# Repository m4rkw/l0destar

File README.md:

# l0destar

[l0destar.com](https://l0destar.com) A fully open-source vehicle tracker - open hardware and open software.

Inspired by the [Geolink Opentracker](https://github.com/geolink/opentracker/) and the [Fortebit Polaris](https://www.fortebit.tech/polaris/), the goal is to build something that will last: a reference design for the best possible vehicle tracker that anyone can fab, modify, and host. Hardware and software are completely open and maintained as a community project.

## Status

Prototyping / design phase. The v2.1 layout worked on a bench, and v2.6 (CAN,
K-line and micro), v3.0, v3.1, v3.2 and v3.3 have since been built and bench
tested - see the test status table in each board's README. v3.4 is designed
but not yet built or tested.

<strong>All boards before v3.3 have a serious defect in the K-wire circuit
if the L wire is connected. If any of these prototypes are built the L wire
should not be connected to the vehicle as if it was ever externally shorted
to the 12V rail the l0destar device would be damaged.</strong> Luckily very
few people are going to care at all about this ancient protocol and even fewer
will ever need the L wire in normal use but it still bears mentioning as an
indication that these are very much prototypes and there may be other
undiscovered defects.

## Disclaimer

This is a prototype, not a product. Nothing here is validated, qualified or certified, the parts lists are examples rather than a verified BOM, and any test results are my own unverified bench observations. All responsibility for anything built from it rests with the person building and installing it.

**Before building, installing or relying on any of this, read the [full disclaimer](DISCLAIMER.md).**

## What it is

- **Mission** - the world's best fully open-source vehicle tracker, no profit motive. See [`MISSION.md`](MISSION.md).
- **Goals** - KiCad reference design, open enclosure CAD, open firmware and server, weeks of standby on a typical car battery, 1 Hz GNSS, LTE-M/NB-IoT, CAN + K-Line diagnostics, accelerometer-driven wake. Full list in [`GOALS.md`](GOALS.md).
- **Technology choices** - Nordic nRF9151 SiP (LTE-M/NB-IoT + GNSS), LT8609A buck, ASM330LHHX IMU, MCP2518FD + TCAN3414 CAN, TJA1027T K-Line. Rationale and trade-offs in [`TECHNOLOGY.md`](TECHNOLOGY.md).

## License

l0destar is multi-licensed by artifact type - permissive across the board:

| Artifact | License |
|---|---|
| Hardware design files | `CERN-OHL-P-2.0` |
| Firmware | `Apache-2.0` |
| Server-side software | `Apache-2.0` |
| Documentation, enclosure CAD, media | `CC-BY-4.0` |

Full text and rationale in [`LICENSE.md`](LICENSE.md); license bodies in [`LICENSES/`](LICENSES/).

## Contributing

Contributions are welcome. l0destar uses the [Developer Certificate of Origin](https://developercertificate.org/) rather than a CLA - every commit must carry a `Signed-off-by:` trailer (`git commit -s`). See [`CONTRIBUTING.md`](CONTRIBUTING.md) for PR expectations.

## Contact

- Bug reports and feature ideas: [GitHub Issues](https://github.com/m4rkw/l0destar/issues)
- Open-ended questions and design discussion: [GitHub Discussions](https://github.com/m4rkw/l0destar/discussions)
- Direct contact: [contact me](https://l0destar.com/contact.html)

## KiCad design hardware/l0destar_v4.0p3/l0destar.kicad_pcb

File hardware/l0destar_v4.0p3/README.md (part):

# l0destar v4.0p3

## Overview

**NOTE: THIS HAS NOT BEEN TESTED, USE AT YOUR OWN RISK**

- This is a prototype l0destar vehicle tracker PCB designed to be
  hand-solderable (hot air required)
- It makes use of the [Makerdiary nRF9151 Connect Kit](https://makerdiary.com/products/nrf9151-connectkit) to provide the LTE and GPS
functions
- Component vias are dogleg-routed deliberately in order to keep the PCB costs
as low as possible
- The RF trace width is calculated using a standard 4-layer stackup at JLCPCB,
  different fabrication processes may require adjustment

## Disclaimer

This is a prototype, not a product. Nothing here is validated or certified,
the parts lists are examples rather than a verified BOM, and any test results
recorded below are my own unverified bench observations - repeat the testing
yourself rather than taking them on trust.

**Before building or installing anything from this repository, read the
[full disclaimer](../../DISCLAIMER.md).**

## New features

- The flash chip now has its own SPI bus
- Rail fault sensing on the GNSS backup supply

## Test status

| Item | Test | Result | Notes |
|---------|------|--------|-------|
| Input stage | 12V input reverse polarity | NOT TESTED | |
| Input stage | 12V ignition input reverse polarity | NOT TESTED | |
| INA238 | Voltage reading function | NOT TESTED | |
| Ignition presence | Ignition sense 3.3v signal | NOT TESTED | |
| LT8609 | 4.2V output | NOT TESTED | |
| LT8609 | UVLO thresholds | NOT TESTED | |
| MCU OVP | 4.2V passes through at nominal voltage | NOT TESTED | S11Q1 on, S12TP2 ≈ the buck output at S6C5 |
| MCU OVP | Cuts off when the buck output (S6C5) is driven above ~5V | NOT TESTED | Trip ≈ 4.95V, release ≈ 4.80V (calculated, see below) |
| MCU OVP | Scope trigger on VBAT rail, should never peak above abs max (~5.5V) during overvoltage condition | NOT TESTED | |
| GPS auxiliary 3.3V rail | Switches on enable signal | NOT TESTED | |
| CAN auxiliary 3.3V rail | Switches on CAN-enable signal | NOT TESTED | |
| K-line auxiliary 3.3V rail | Switches on K-enable signal | NOT TESTED | |
| K-line auxiliary 12V rail | Switches on K-enable signal | NOT TESTED | |
| Accelerometer | Operates while awake | NOT TESTED | |
| Accelerometer | Wake on motion | NOT TESTED | |
| GPS antenna bias tee | Obtains GPS signal | NOT TESTED | |
| K-wire | K wire connectivity | NOT TESTED | |
| CAN | Connectivity | NOT TESTED | |
| CAN standby via XSTBY signal | Low standby current | NOT TESTED | |
| Board | Quiescent current, GNSS backup supply off | | |
| Board | Quiescent current, GNSS backup supply on | | Reduces the TTFF from 17s to around 3s |

Note: the GNSS backup supply can be configured to enable on the first drive of a
day and then disable after a specific time (eg midnight) in order to conserve
power.

## Features

 - 12V live and 12V ignition inputs with TVS and reverse polarity protection
 - Enhanced input protection sized for pulse 2a at the ISO 7637-2:2011 maximum
 - Onboard 2A fusing
 - Ignition presence sensing
 - INA238 voltage reading
 - High efficiency buck converter
 - Auxiliary 3.3V rail for the GPS antenna bias tee
 - ASM330LHHXTR 6-axis IMU gyro/accelerometer
 - USB-C can be connected and disconnected for programming without any power
   disruption
 - Optional CAN interface
 - Optional K-wire (ISO 14230-1 K-line) interface - the wire carries KWP2000 (ISO 14230-4), the older
   ISO 9141-2, and manufacturer-specific pre-OBD protocols such as VAG KW1281
 - Auxiliary rail sensing/fault detection
 - MCU over-voltage protection on the 4.2V rail with fault-injection test point
 - I2C bus filtering against LTE TX bursts
 - Dedicated U-blox GPS module supporting BeiDou, Galileo, GLONASS, GPS / QZSS
- MX25R6435FZNIL0 64Mbit (8MB) SPI flash for data buffering / config

## Changes from v4.0p2

- K\_SLEEP tied to a pullup as there's no need for this to be GPIO controlled
- GNSS\_TIMEPULSE removed as this isn't used
- The flash chip no longer shares an SPI bus with the CAN circuit
- Added rail fault sensing on the GNSS backup supply

## Power supply

The Connect Kit can be powered through VBUS which would be much simpler as it
can take 5V, but then you have to disconnect the power before connecting a USB
cable. Same for the Nordic dev board - they both explicitly say not to connect
powered USB and VBUS at the same time. Because the intention is to install this
in a vehicle for testing the pragmatic decision was taken to power it with a
4.2V buck feeding the battery connector. With this power connection we can
connect USB-C at any time to update the firmware without needing to disconnect
power.

## Notes

 - All caps on the 12V rails must be >= 50V in order to handle transients
 - MCP2518FD with PP3V3\_CAN off - abs max on all I/O is VDD + 0.3V. Firmware
   must drive CAN\_SCK/SDI/CS low or tri-state them before dropping
   CAN\_ENABLE, or the nRF backfeeds the dead rail through the clamp diodes.
   Additionally, CAN\_CS and CAN\_INT have their pull-ups (S9R1, S9R2) on the
   switched rail, so both float when the domain is off - enable the nRF
   internal pulldown on those pins
 - K-line side, now its own domain - K\_ENABLE gates PP3V3\_K and PP12V\_K
   together. K\_TX lands on the TJA1027T, which is supplied from PP12V\_K
   (VBAT, pin 7), so driving it high with the rail down backfeeds the
   transceiver through its ESD clamps. K\_TX and K\_RX also carry 10K pull-ups
   (S10R2, S10R1) to PP3V3\_K, which float when that rail is down. Firmware
   must park K\_TX/K\_RX (low or tri-state) before dropping K\_ENABLE
 - The TJA1027T SLP\_N pin is not GPIO controlled: it is tied to PP3V3\_K
   through a 100K pull-up (S10R6), so the transceiver is awake whenever the
   K-line domain is powered. K\_ENABLE is the only way to put it to sleep
 - The OVP stage latches off while the unprotected rail stays above the
   release threshold. If the buck is genuinely faulted it will stay off; to
   clear a transient trip the input power has to drop far enough for the buck
   output to fall below ~4.8V
 - What the trip point has to protect: the 4.2V rail lands on the Connect Kit's
   battery connector (J2, MX1.25-2P), which goes to the **BAT pin of its
   BQ25180 charger** - not to the nRF9151 directly. On the BQ25180 only the IN
   pin is 25V tolerant; BAT and SYS are rated -0.3V to 5.5V absolute maximum.
   With no USB attached the BATFET conducts BAT to SYS, and SYS feeds nRF9151
   VDD through ferrite L4, so an over-voltage reaches the SiP as well - and the
   nRF9151 VDD absolute maximum is also 5.5V (VDD\_GPIO is a separate rail at
   3.9V). So 5.5V is the ceiling on both counts
 - S11R5/S11R6 set the trip point: V\_trip ≈ 2.5V × (1 + S11R5/S11R6) shifted
   slightly by S11R3. Nominal trip is ≈4.95V; worst case over the ATL431B's
   0.5% reference, 1% on S11R5/S11R6 and 5% on S11R3 the window is ≈4.87V to
   5.02V, so it stays clear of the buck's nominal 4.24V plus ripple at the
   bottom and keeps ~0.48V of margin to the 5.5V ceiling at the top. Keep the
   divider at 1% - a 5% pair widens that window at both ends
 - Indicated voltages and tolerances are the minimum, I generally always buy the
   tightest tolerances and highest voltages possible of everything as it's just
   simpler for managing inventory. Because of this, several of the "example"
   links will be to the parts I bought which might be tighter tolerance or
   higher voltage rating than the indicated minimum spec

## Bill of materials - required

| Item | Description | Specification | Example | Notes |
|------|-------------|---------------|---------|-------|
| MCU | MCU and GSM/GPS 40pin board | nRF9151 Connect Kit | [Makerdiary nRF9151 Connect Kit](https://makerdiary.com/products/nrf9151-connectkit) | |
| S1J1 | Molex Micro-fit 3.0 2x03 PCB connector | 43045-0600 | [43045-0600](https://uk.farnell.com/molex/43045-0600/conn-r-a-pcb-hdr-6pos-2row-3mm/dp/1012252) | |
| S1J2 | Makerdiary header 1 | 20-pin 2.54mm header | [20-pin pcb header](https://www.aliexpress.com/item/1005003610333849.html) | |
| S1J3 | Makerdiary header 2 | 20-pin 2.54mm header | [20-pin pcb header](https://www.aliexpress.com/item/1005003610333849.html) | |
| S1R1 | I2C pull-up resistor | 0402 1.8K 1% | [MCMR04X1801FTL](https://uk.farnell.com/multicomp-pro/mcmr04x1801ftl/res-1k8-1-0-0625w-0402-ceramic/dp/2072709) | |
| S1R2 | I2C pull-up resistor | 0402 1.8K 1% | [MCMR04X1801FTL](https://uk.farnell.com/multicomp-pro/mcmr04x1801ftl/res-1k8-1-0-0625w-0402-ceramic/dp/2072709) | |
| S1R3 | 100K pulldown resistor | 0402 100K 5% | [MCPWR02FTEP1003A](https://uk.farnell.com/multicomp-pro/mcpwr02ftep1003a/res-100k-1-thick-film-0402/dp/4538624) | |
| S1R4 | 100K pulldown resistor | 0402 100K 5% | [MCPWR02FTEP1003A](https://uk.farnell.com/multicomp-pro/mcpwr02ftep1003a/res-100k-1-thick-film-0402/dp/4538624) | |
| S1R5 | 100K pulldown resistor | 0402 100K 5% | [MCPWR02FTEP1003A](https://uk.farnell.com/multicomp-pro/mcpwr02ftep1003a/res-100k-1-thick-film-0402/dp/4538624) | |
| S1C1 | 100nF capacitor | 0402 >= 50V 10% X7R | [GRM155R71H104KE14D](https://uk.farnell.com/murata/grm155r71h104ke14d/cap-0-1-f-50v-10-x7r-0402/dp/2611912) | |
| S2F1 | 2A fuse | 1206 2A slow blow | [0407002.WRA](https://www.ebay.co.uk/itm/178539955750) | |
| S2F2 | 2A fuse | 1206 2A slow blow | [0407002.WRA](https://www.ebay.co.uk/itm/178539955750) | |
| S2Q1 | Reverse-polarity MOSFET | SQ2361 SOT-23 | [SQ2361CES-T1_BE3](https://www.ebay.co.uk/itm/178539853850) | |
| S2Q2 | Reverse-polarity MOSFET | SQJ457EP-T1_BE3 | [SQJ457EP-T1-GE3](https://www.ebay.co.uk/itm/178539865485) | |
| S2D1 | 15V Zener diode | BZX84C15 | [BZX84C15](https://uk.farnell.com/multicomp-pro/bzx84c15/zener-diode-0-3w-15v-sot-23/dp/2675186) | |
| S2D2 | 400W TVS diode | PTVS33VS1UTR,115 SOD-123W | [PTVS33VS1UTR,115](https://www.ebay.co.uk/itm/178539916580) | |
| S2D3 | 15V Zener diode | BZX84C15 | [BZX84C15](https://uk.farnell.com/multicomp-pro/bzx84c15/zener-diode-0-3w-15v-sot-23/dp/2675186) | |
| S2D4 | 400W TVS diode | PTVS33VS1UTR,115 SOD-123W | [PTVS33VS1UTR,115](https://www.ebay.co.uk/itm/178539916580) | |
| S2R1 | Pulldown resistor | 0402 1M 5% | [ERJ2RKF1004X](https://uk.farnell.com/panasonic/erj2rkf1004x/res-1m-1-0-1w-0402-thick-film/dp/2302957) | |
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
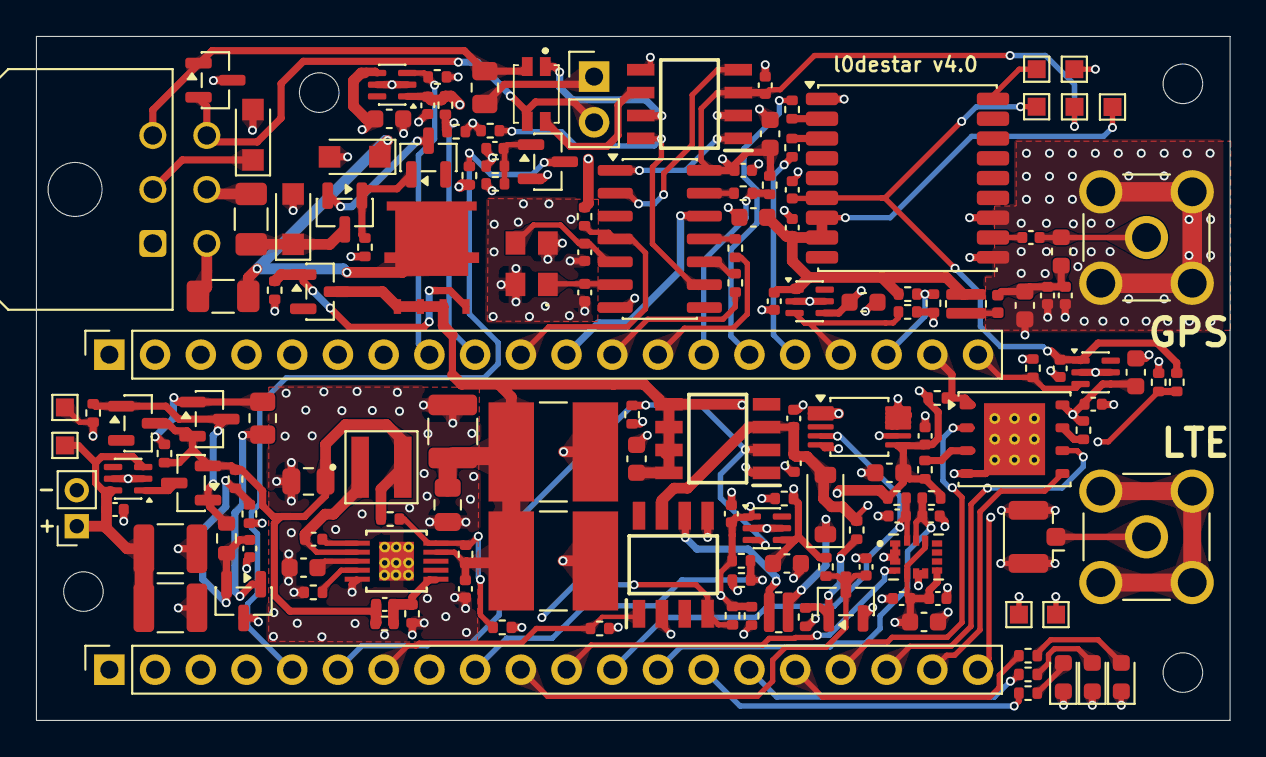
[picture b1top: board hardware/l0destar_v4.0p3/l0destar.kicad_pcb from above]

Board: 4 copper layers, 66.3 x 38.0 mm, 161 parts (0 on the bottom side), 89 nets.

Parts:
H1, H2, H3, H4: MountingHole; MountingHole_2.2mm_M2
S1C1, S3C2, S4C1, S6C1, S6C8, S7C2, S7C4, S7C9, S8C1, S8C3, S9C1, S9C4, S10C1, S16C2, S16C4, S16C5, S17C1: 0402 100nF 50V 10% X7R; C_0402_1005Metric
S1J1: Main connector; Molex_Micro-Fit_3.0_43045-0600_2x03_P3.00mm_Horizontal
S1J2: Conn_01x20_Socket; MakerDiary_nRF9151_ConnectKit_PinHeader_1-20_tight
S1J3: Conn_01x20_Socket_21-40; MakerDiary_nRF9151_ConnectKit_PinHeader_21-40_tight
S1J4: +; MakerDiary2PinHeader
S1R1, S1R2: 0402 1.8K 1%; R_0402_1005Metric
S1R3, S1R4, S1R5, S2R2, S7R3, S7R6, S7R7, S7R8, S7R10, S10R6, S16R1, S16R4: 0402 100K 5%; R_0402_1005Metric
S2C1, S2C2: 47uF 2220 50V 20% X7R; CAPC6050X550N
S2C3: 10uF 1210 50V 10% X7R SOFT TERMINATION; C_1210_3225Metric
S2D1, S2D3, S11D1: BZX84C15; SOT-23
S2D2, S2D4, S10D2: PTVS33VS1UTR,115; Nexperia_CFP3_SOD-123W
S2F1, S2F2: 0407002.WRA; Fuse_1206_3216Metric
S2Q1, S11Q1: SQ2361CES-T1_BE3; SOT-23
S2Q2: SQJ457EP-T1_BE3; POWERPAK-SO-8-4
S2R1, S7R4, S7R9, S7R11, S16R5: 0402 1M 5%; R_0402_1005Metric
S3C1, S6C2, S7C1, S7C3, S7C8, S15C4, S16C1, S16C3: 0603 2.2uF 25V 10% X7R; C_0603_1608Metric
S3U1: INA238; TSSOP-10_3x3mm_P0.5mm
S4Q1, S7Q1: 2N7002; SOT-23
S4R1, S7R5: 0402 180K 5%; R_0402_1005Metric
S4R2, S4R3: 0402 56K 5%; R_0402_1005Metric
S6C3: 0805 4.7uF 50V 10% X7R; C_0805_2012Metric
S6C4: 0402 10pF 50V C0G/NP0; C_0402_1005Metric
S6C5: 0805 22uF 10V 20% X7R; C_0805_2012Metric
S6L1: XFL4020-222ME; IND_XFL4020-222ME
S6R1: 0402 18.2K 1%; R_0402_1005Metric
S6R2: 0402 226K 1% ANTI-SULFUR AEC-Q200; R_0402_1005Metric
S6R3, S11R5: 0402 1M 1% ANTI-SULFUR AEC-Q200; R_0402_1005Metric
S6R4: 0402 0R JUMPER OR 1M 1% ANTI-SULFUR AEC-Q200; R_0402_1005Metric
S6R5: DNP 0402 243K 1% ANTI-SULFUR AEC-Q200; R_0402_1005Metric
S6R6: DNP 0402 3.92M 1%; R_0402_1005Metric
S6U1: LT8609AIMSE_PBF; LT8609AIMSE_WITH_GROUND_VIAS
S7C5, S7C7: 0402 1nF 50V 10% X7R; C_0402_1005Metric
S7C6: 0603 220nF 50V 10% X7R; C_0603_1608Metric
S7U1, S7U2, S7U4, S16U1: SiP32431DR3; SOT-363_SC-70-6
S7U3: ITS4060SSJNXUMA1
S8C2, S9C5: 0603 10uF 10V 20% X7R; C_0603_1608Metric
S8C4, S8C5, S15C2: 0402 100pF 50V 5% C0G/NP0; C_0402_1005Metric
S8R1: 0402 FB BLM15AG601SH1D; R_0402_1005Metric
S8U1: ASM330LHHXTR; XDCR_ASM330LHHXTR
S9C2, S9C3: 0402 27pF 10V 5% C0G/NP0; C_0402_1005Metric
S9D1: NUP2105L; SOT-23
S9FL1: ACT1210-101-2P-TL00; ACT12101012PTL00_tight
S9J1: Conn_01x02_Pin; PinHeader_1x02_P2.54mm_Vertical_Tight
S9R1, S9R2, S9R4, S10R1, S10R2, S17R1, S17R2, S17R3: 0402 10K 5%; R_0402_1005Metric
S9R3: 0805 120R 5% 0.5W; R_0805_2012Metric
S9R5, S13R1, S13R2, S13R3, S16R2, S16R3: 0402 1K 5%; R_0402_1005Metric
S9R6, S9R7: 0402 220R 5%; R_0402_1005Metric
S9U1: TCAN3414DR; SOIC127P600X175-8N
S9U2: MCP2518FD-xQBB; SOIC-14_3.9x8.7mm_P1.27mm
S9Y1: ECS-400-18-33-JGN-TR3; ECS4001833JGNTR3
S10D1: 1N4148W; D_SOD-123
S10R3: 0508 510R 5% 1W; R_0508_1220Metric_WideTerminal_Tight
S10U1: TJA1027T_20,118; TJA1027T_20_118
S11C1, S11C2: 1210 47uF 10V 20% X7R; C_1210_3225Metric
S11C3: 0402 3.3pF 50V C0G/NP0 +/- 0.25pF; C_0402_1005Metric
S11Q2: BC856BLT1G; SOT-23
S11R1: 0402 10K 1%; R_0402_1005Metric
S11R2: 0402 1M 1%; R_0402_1005Metric
S11R3: 0603 33M 5%; R_0603_1608Metric
S11R4: 0805 15K 1% ANTI-SULFUR AEC-Q200; R_0805_2012Metric
S11R6: 0402 1.05M 1%; R_0402_1005Metric
S11U1: LM66100DCK; SOT-363_SC-70-6
S11U2: ATL431BQDBZR; SOT-23
S12TP1: GND; TestPoint_Pad_1.0x1.0mm
S12TP2: 4.2V protected; TestPoint_Pad_1.0x1.0mm
S12TP3: 3.3V; TestPoint_Pad_1.0x1.0mm
S12TP4: 3.3V GNSS BCKP; TestPoint_Pad_1.0x1.0mm
S12TP5: 3.3V CAN; TestPoint_Pad_1.0x1.0mm
S12TP6: 3.3V K; TestPoint_Pad_1.0x1.0mm
S12TP7: 12V K; TestPoint_Pad_1.0x1.0mm
S13D1, S13D2, S13D3: Wurth 150060RS86000; LED_0603_1608Metric
S15C1: 0402 47pF 50V 5% C0G/NP0; C_0402_1005Metric
S15C3: 0402 10nF 50V 5% C0G/NP0; C_0402_1005Metric
S15FB1: 0402 600R 0.5A 25%; L_0402_1005Metric
S15J2: GPS_SMA; SAMTEC_SMA-J-P-H-RA-TH1_centrepin
S15J3: GSM_UFL; U.FL_Hirose_U.FL-R-SMT-1_Vertical
S15J4: GSM_SMA; SAMTEC_SMA-J-P-H-RA-TH1_centrepin
S15L1: LQW18AN68NJ00D; L_0603_1608Metric
S15R1: 0508 1W 5% 15R; R_0508_1220Metric_WideTerminal_Tight
S16TP1: 3.3V GNSS; TestPoint_Pad_1.0x1.0mm
S16TP2: SAFEBOOT_N; TestPoint_Pad_1.0x1.0mm
S16U2: MAX-M10S; ublox_MAX
S17U1: MX25R6435FZNIL0; WSON-8-1EP_6x5mm_P1.27mm_EP3.4x4mm_with_vias

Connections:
/FLASH_RESET: S17R3.2, S17U1.7 (~RESET/SIO3)
/FLASH_WP: S17R2.2, S17U1.3 (~WP/SIO2)
ACCELL_INT1: S1J2.11, S8U1.4 (INT1)
CAN_CS: S1J3.27 (Pin_14), S9R1.2, S9R5.1
CAN_ENABLE: S1J3.33 (Pin_8), S1R4.2, S7U2.3 (ON)
CAN_H: S1J1.3, S9D1.1 (K), S9FL1.2, S9R3.2
CAN_INT: S1J3.31 (Pin_10), S9R2.2, S9U2.4 (~INT)
CAN_L: S1J1.6, S9D1.2 (K), S9FL1.3, S9J1.2
CAN_SCK: S1J3.29 (Pin_12), S9R6.1
CAN_SDI: S1J3.28 (Pin_13), S9R7.1
CAN_SDO: S1J3.30 (Pin_11), S9U2.12 (SDO)
FLASH_CS: S1J3.22 (Pin_19), S17R1.2, S17U1.1 (~CS)
FLASH_SCK: S1J2.18, S17U1.6 (SCLK)
FLASH_SDI: S1J2.19, S17U1.5 (SI/SIO0)
FLASH_SDO: S1J2.17, S17U1.2 (SO/SIO1)
GND: S1C1.1, S1J1.1, S1J2.3 (GND), S1J3.39 (Pin_2), S1J4.2, S1R3.1, S1R4.1, S1R5.1, S2C1.2, S2C2.2, S2C3.2, S2D2.2 (A), S2D4.2 (A), S2R1.2, S2R2.2, S3C1.1, S3C2.1, S3U1.1 (A1), S3U1.2 (A0), S3U1.7 (GND), S4C1.2, S4Q1.2 (S), S4R2.1, S6C2.2, S6C3.2, S6C5.2, S6C8.2, S6R1.2, S6R2.2, S6R5.1, S6U1.5 (SYNC), S6U1.11 (GND), S7C1.2, S7C2.2, S7C3.2, S7C4.2, S7C5.2, S7C6.2, S7C7.2, S7C8.2, S7C9.2, S7Q1.2 (S), S7R4.1, S7R6.1, S7R9.1, S7R11.1, S7U1.2 (GND), S7U1.5 (GND), S7U2.2 (GND), S7U2.5 (GND), S7U3.1 (GND), S7U4.2 (GND), S7U4.5 (GND), S8C1.2, S8C2.2, S8C3.2, S8C4.2, S8C5.2, S8U1.1 (SDO/SA0), S8U1.2 (MSDA), S8U1.3 (MSCL), S8U1.6 (NC), S8U1.7 (GND), S9C1.2, S9C2.2, S9C3.2, S9C4.2, S9C5.2, S9D1.3 (A), S9R4.2, S9U1.2 (GND), S9U1.5 (SHDN), S9U2.7 (VSS), S9Y1.2 (GND_1), S9Y1.4 (GND_2), S10C1.1, S10D2.2 (A), S10U1.5 (GND), S11C1.2, S11C2.2, S11C3.1, S11R2.1, S11R6.1, S11U1.2 (GND), S11U1.5 (ST), S11U2.3 (ANODE), S12TP1.1 (1_1), S13D1.1 (K), S13D2.1 (K), S13D3.1 (K), S15C2.2, S15C3.2, S15C4.2, S15J2.2, S15J2.3, S15J2.4, S15J2.5, S15J3.2 (Ext), S15J4.2, S15J4.3, S15J4.4, S15J4.5, S16C1.2, S16C2.2, S16C3.2, S16C4.2, S16C5.2, S16R1.2, S16R5.2, S16U1.2 (GND), S16U1.5 (GND), S16U2.1 (GND), S16U2.10 (GND), S16U2.12 (GND), S17C1.2, S17U1.4 (GND), S17U1.9 (GND)
GNSS_BCKP_EN: S1J3.21 (Pin_20), S1R3.2, S7U1.3 (ON)
GNSS_ENABLE: S1J3.24 (Pin_17), S16R1.1, S16U1.3 (ON)
GNSS_RF: S15C1.1, S16U2.11 (RF_IN)
GNSS_RX: S1J3.26 (Pin_15), S16R2.1
GNSS_TX: S1J3.25 (Pin_16), S16R3.1
I2C_SCL: S1J2.13, S1R2.1, S3U1.5 (SCL), S8C5.1, S8U1.13 (SCL)
I2C_SDA: S1J2.12, S1R1.1, S3U1.4 (SDA), S8C4.1, S8U1.14 (SDA)
IGN_SENSE: S1J2.5 (P9), S4Q1.3 (D), S4R3.2
KWIRE_K: S1J1.2, S10D2.1 (K), S10R3.2, S10U1.6 (LIN)
K_ENABLE: S1J2.6, S1R5.2, S7U3.2 (IN), S7U4.3 (ON)
K_RX: S1J2.7, S10R1.2, S10U1.1 (RXD)
K_TX: S1J2.8, S10R2.2, S10U1.4 (TXD)
LED1: S1J2.14, S13R1.2
LED2: S1J2.15, S13R2.2
LED3: S1J2.16, S13R3.2
unnamed: S2D1.1 (A), S2Q1.1 (G), S2R1.1
unnamed: S2D2.1 (K), S2F1.1, S2Q1.3 (D)
unnamed: S2D3.1 (A), S2Q2.4, S2R2.1
unnamed: S2D4.1 (K), S2F2.2, S2Q2.5_0, S2Q2.5_1, S2Q2.5_2, S2Q2.5_3
unnamed: S4C1.1, S4Q1.1 (G), S4R1.2, S4R2.2
unnamed: S6C1.1, S6U1.1 (BST)
unnamed: S6R4.1, S6R5.2, S6R6.2, S6U1.10 (EN/UV)
unnamed: S6C4.1, S6R2.1, S6R3.1, S6U1.6 (FB)
unnamed: S6C2.1, S6U1.3 (INTVCC)
unnamed: S6R1.1, S6U1.4 (RT)
unnamed: S6C1.2, S6L1.1, S6U1.2 (SW)
unnamed: S7Q1.1 (G), S7R5.2, S7R6.2
unnamed: S8C1.1, S8C2.1, S8C3.1, S8R1.2, S8U1.5 (VDD_IO), S8U1.8 (VDD), S8U1.12 (CS)
unnamed: S9J1.1, S9R3.1
unnamed: S9FL1.1, S9U1.7 (CANH)
unnamed: S9FL1.4, S9U1.6 (CANL)
unnamed: S9U1.4 (RXD), S9U2.2 (RXCAN)
unnamed: S9R4.1, S9U1.8 (STBY), S9U2.9 (~INT0/GPIO0/XSTBY)
unnamed: S9U1.1 (TXD), S9U2.1 (TXCAN)
unnamed: S9C3.1, S9U2.6 (OSC1), S9Y1.1 (IN/OUT)
unnamed: S9C2.1, S9U2.5 (OSC2), S9Y1.3 (OUT/IN)
unnamed: S9R6.2, S9U2.10 (SCK)
unnamed: S9R7.2, S9U2.11 (SDI)
unnamed: S9R5.2, S9U2.13 (~CS)
unnamed: S10D1.1 (K), S10R3.1
unnamed: S10R6.1, S10U1.2 (SLP_N)
unnamed: S11D1.1 (A), S11Q1.1 (G), S11Q2.3, S11R2.2, S11R3.2
unnamed: S11Q2.1, S11R1.1, S11R4.2
unnamed: S11R4.1, S11U2.1 (CATHODE)
unnamed: S11C3.2, S11R3.1, S11R5.2, S11R6.2, S11U2.2 (REF)
unnamed: S13D1.2 (A), S13R1.1
unnamed: S13D2.2 (A), S13R2.1
unnamed: S13D3.2 (A), S13R3.1
unnamed: S15C2.1, S15C3.1, S15C4.1, S15FB1.2, S15L1.1
unnamed: S15FB1.1, S15R1.1
unnamed: S15J3.1 (In), S15J4.1
unnamed: S16R3.2, S16U2.3 (RXD)
unnamed: S16R2.2, S16U2.2 (TXD)
unnamed: S16TP2.1 (1_1), S16U2.18 (~SAFEBOOT)
PP3V3: S1J3.40 (Pin_1), S1R1.2, S1R2.2, S3C1.2, S3C2.2, S3U1.6 (VS), S4R3.1, S7C1.1, S7C3.1, S7C8.1, S7R7.2, S7U1.4 (IN), S7U2.4 (IN), S7U4.4 (IN), S8R1.1, S12TP3.1 (1_1), S16C1.1, S16U1.4 (IN), S17C1.1, S17R1.1, S17R2.1, S17R3.1, S17U1.8 (VCC)
PP3V3_CAN: S7C4.1, S7R3.1, S7U2.1 (OUT), S9C1.1, S9C4.1, S9C5.1, S9R1.1, S9R2.1, S9U1.3 (VDD), S9U2.14 (VDD), S12TP5.1 (1_1)
PP3V3_CAN_ST: S1J3.32 (Pin_9), S7R3.2, S7R4.2
PP3V3_GNSS: S15R1.2, S16C2.1, S16C3.1, S16C4.1, S16R4.1, S16TP1.1 (1_1), S16U1.1 (OUT), S16U2.7 (VCC_IO), S16U2.8 (VCC)
PP3V3_GNSS_BCKP: S7C2.1, S7R10.1, S7U1.1 (OUT), S12TP4.1 (1_1), S16C5.1, S16U2.6 (V_BCKP)
PP3V3_GNSS_BCKP_ST: S1J2.20, S7R10.2, S7R11.2
PP3V3_GNSS_ST: S1J3.23 (Pin_18), S16R4.2, S16R5.1
PP3V3_K: S7C9.1, S7R8.1, S7U4.1 (OUT), S10R1.1, S10R2.1, S10R6.2, S12TP6.1 (1_1)
PP3V3_K_ST: S1J2.9, S7R8.2, S7R9.2
PP4V2: S1C1.2, S1J4.1, S11C1.1, S11C2.1, S11U1.3 (~CE), S11U1.6 (VOUT), S12TP2.1 (1_1)
PP4V2_OVP_PROTECTED: S11Q1.3 (D), S11U1.1 (VIN)
PP4V2_UNPROTECTED: S6C4.2, S6C5.1, S6L1.2, S6R3.2, S6R6.1, S11D1.3 (K), S11Q1.2 (S), S11Q2.2, S11R1.2, S11R5.1
PP12V: S1J1.4, S2F2.1
PP12VI: S1J1.5, S2F1.2
PP12VIP: S2D1.3 (K), S2Q1.2 (S), S4R1.1
PP12VP: S2C1.1, S2C2.1, S2C3.1, S2D3.3 (K), S2Q2.1, S2Q2.2, S2Q2.3, S3U1.8 (Vbus), S3U1.9 (Vin-), S3U1.10 (Vin+), S6C3.1, S6C8.1, S6R4.2, S6U1.9 (VIN), S7C6.1, S7U3.5 (VS_1), S7U3.6 (VS_2), S7U3.7 (VS_3), S7U3.8 (VS_4)
PP12V_K: S7C5.1, S7R5.1, S7U3.3 (OUT), S10C1.2, S10D1.2 (A), S10U1.7 (VBAT), S12TP7.1 (1_1)
PP12V_K_ST: S1J2.10, S7C7.1, S7Q1.3 (D), S7R7.1
RF: S15C1.2, S15J2.1, S15L1.2

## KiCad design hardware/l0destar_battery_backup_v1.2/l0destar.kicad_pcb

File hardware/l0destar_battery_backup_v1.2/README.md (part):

# l0destar battery backup v1.2

## Overview

- This is a prototype inline battery backup module for the l0destar vehicle
  tracker. It sits in the harness between the car and the tracker and holds
  the tracker's supply at ~9V from a single CR123A lithium primary cell when
  car power is cut
- It is designed to be hand-solderable (hot air required). Every active part
  is in a leaded package: MSOP-12, SOT-23, TSOT-23, SC70, DPAK
- The cell is a **non-rechargeable** primary in a board-mounted holder.
  Nothing on the board charges it. See [Why a primary cell](#why-a-primary-cell)
- Pin-compatible with the v3.4 tracker's 2x3 Micro-Fit harness: J1 takes the
  car harness, J2 goes to the tracker, the CAN/K-line pins pass straight
  through and ignition passes through a diode (S1D1)
- 4-layer 63.1 x 36.2 mm board, JLC04161H-7628 stack-up, four M2 mounting
  holes. PCB DRC is clean and schematic ERC has only the cosmetic
  `endpoint_off_grid` warnings

## Changes from v1.1

1. External pin assignments updated for v4.0 boards

## Disclaimer

This is a prototype, not a product. Nothing here is validated or certified,
the parts lists are examples rather than a verified BOM, and every number
below is a desk calculation from datasheets rather than a bench measurement -
repeat the testing yourself rather than taking any of it on trust.

I strongly recommend not using unbranded CR123 cells or buying them from less
reputable sources.

**Before building or installing anything from this repository, read the
[full disclaimer](../../DISCLAIMER.md).**

## Test status

| Item | Test | Result | Notes |
|---------|------|--------|-------|
| Input stage | 12V car input reverse polarity | PASSED | S2Z1 conducts forward into S2F1, which should clear |
| Input stage | Pass-through drop VCAR to PPTRACKER, tracker asleep | PASSED | v1.0 dropped ~0.5V here. Expected ~20 mV, the LTC4412 regulated forward drop |
| Input stage | Pass-through drop VCAR to PPTRACKER at 50 mA and 250 mA | PASSED | Expected ~20 mV; S2Q1 is 15 mΩ so the regulation sets it, not R<sub>DS(on)</sub> |
| Switchover | Boost enables when the car rail falls below ~10.06V | PASSED | S6U1 with the 6.8M/909k divider |
| Switchover | Boost disables when the car rail returns above ~11V | PASSED | Depends on the cell voltage through S6R38/S6R39, see [Notes](#notes) |
| Boost | 9.6V output at S4C14/S4C15 | PASSED | 1.202V x (1 + 909k/130k) = 9.61V; ~9V at J2 after S2D2 |
| Cell | Reversed cell is harmless | PASSED | Not physically possible to install the cell backwards |
| Cell | No current ever flows into the cell | PASSED | Ammeter in series with the cell with the car present and during handover |
| Wake pulse | IGN pulse at boost start, car ignition wire connected and off | PASSED | Failed on v1.0. Expected ~12V peak, above 8V for ~0.4 s, at J2 pin 5, with S1D1 blocking the car pulldown |
| Wake pulse | Car ignition reaches the tracker | PASSED | J2 pin 5 should be one S1B drop below J1 pin 5 with the key on |
| Wake pulse | Sleeping tracker wakes and raises `backup power` | PASSED | Needs firmware with `CONFIG_APP_BACKUP_SUPPLY=y` |
| Board | Parked drain from the car with the cell fitted | PASSED | ~15 µA on top of the tracker's own draw |

## Features

 - Inline between the car harness and the tracker; CAN/K-line pass straight
   through, ignition through S1D1
 - ~15 µA quiescent draw from the car in pass-through: ~13 µA LTC4412HV plus
   the ~1.6 µA sense divider
 - Same input protection parts as the tracker: 2A time-lag fuse, 33V TVS
   sized to ride out suppressed load dump
 - Reverse polarity protection
 - Ideal diode pass-through (LTC4412HV + P-channel FET) with a ~20 mV drop
   down to sleep current
 - Synchronous boost (LTC3122) with true output disconnect: the backup rail
   is 0V while the car is present, so the cell is only ever loaded during a
   cut
 - Nanopower comparator switchover (TLV3012, 2.8 µA) running straight from
   the cell: takes over below ~10.06V on the car rail
 - No cell lockout: the boost runs the cell until it can't. It's a
   consumable primary, so there is nothing to protect
 - Ignition wake pulse: a cut wakes a sleeping tracker immediately instead of
   at its next timed wake, and the tracker reports the cut
 - Estimated runtime on a 1500 mAh CR123A: ~200 days idle, ~58 days
   reporting hourly, ~19 days reporting every 15 minutes
 - 3D-printable two-part enclosure with the cell accessible under the lid

## Why a primary cell

A non-rechargeable cell rather than a rechargeable pack, for three reasons:

- No rechargeable 18650-format cell is rated for storage in a sun-parked car.
  The binding limit is storage temperature (+45 °C at best for Li-ion and LFP;
  +20 °C beyond three months for LTO) and a parked car reaches ~70 °C cabin
  air. A CR123A is rated to +60/+70 °C
- Cycle life is not worth paying for. The backup cycles a handful of times a
  year
- A primary turns silent ageing into an event. The boost regulates its output,
  so the tracker cannot see cell voltage - a rechargeable's calendar fade would
  be invisible until a real theft tested it. The only thing that consumes a
  primary is a power cut the tracker already alerts on, so *"did it get
  used?"* is answered in the server's alert log

The cell is a consumable. A `backup power` alert that runs for a long time
means the cell needs replacing, since it does not recover. Taking the cell
out is the storage mode.

### Ignition wake pulse

A sleeping tracker has three wake sources: its timer, the accelerometer and
ignition-present. A power cut touches none of them, so on its own it would be
found at the next timed wake. The module therefore fakes ignition for a
moment when it takes over.

The tracker's wake is level-triggered and the firmware latches it, so the
pulse only has to trip the interrupt. On an ignition wake the firmware reads
the rail first: in the backup band it is the module's pulse, so the unit
reports at once with the `backup power` alert and goes back to sleep.

The car holds its ignition wire at ground when the key is off, which sank
the pulse on v1.0. S1D1 sits in series between the car's ignition (J1 pin 5)
and the tracker's (J2 pin 5) so the pulse only drives the tracker's input.
The cost is one silicon diode drop on the ignition signal the tracker sees.

Limits: a second cut within the ~40 s VBOOST decay gives no pulse and falls
back to the timed wake.

## Board configuration

### Connectors

Both connectors are the tracker's Molex Micro-Fit 3.0 2x3 (43045-0600) with
the v3.4 pinout. J1 is the car harness, J2 goes to the tracker.

| Pin | J1 (car) | J2 (tracker) | Notes |
|-----|----------|--------------|-------|
| 1 | SPARE | SPARE | Unused by v3.4, not connected on this board |
| 2 | GND | GND | |
| 3 | CAN\_H / K | CAN\_H / K | Passed straight through |
| 4 | +12V | +12V (PPTRACKER) | Car through the ideal diode, or ~9V from the boost on backup |
| 5 | IGN | IGN | Through S1D1 (one diode drop); the wake pulse is injected on the J2 side |
| 6 | CAN\_L / L | CAN\_L / L | Passed straight through |

### Firmware

The tracker needs `CONFIG_APP_BACKUP_SUPPLY=y`. With it, a supply between
`CONFIG_APP_BACKUP_MIN_MV` (8500) and `CONFIG_APP_BACKUP_MAX_MV` (9700) with
the ignition off is treated as backup power rather than a flat car battery:
timed reports keep going, the 11.8V power-off and 12.0V sleep-safety rules
are bypassed, a `backup power` alert is raised once and a `car power
restored` alert when the rail comes back. Without the module a car battery in
that band is flat, so leave it off on trackers that do not have one.

### Cell

The board carries a Keystone 1051 CR123A holder and nothing else as a cell
input. Fit a CR123A from one of the three big brands (Energizer 123 /
EL123AP, Panasonic CR123A, Duracell DL123A): all are high-rate Li-MnO2 cells,
1500-1550 mAh, rated for the ~130 mA typical / ~250 mA worst-case bursts the
boost draws. Mark polarity on the silk and the lid; a reversed cell is
harmless but gives no backup.

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
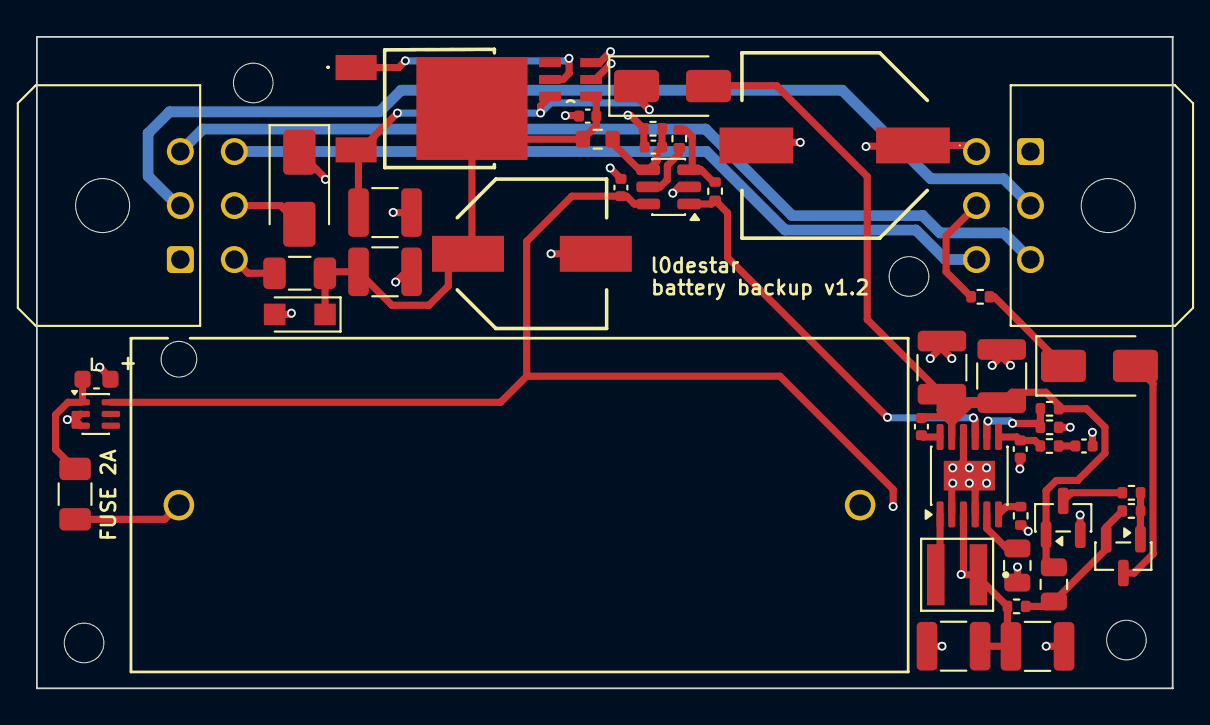
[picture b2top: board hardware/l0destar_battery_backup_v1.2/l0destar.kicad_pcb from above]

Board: 4 copper layers, 63.1 x 36.2 mm, 50 parts (0 on the bottom side), 30 nets.

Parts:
S1D1, S2D2, S5D3: S1B; D_SMA
S1H1, S1H2, S1H3, S1H4: MountingHole; MountingHole_2.2mm_M2
S1J1: Car harness; Molex_Micro-Fit_3.0_43045-0600_2x03_P3.00mm_Horizontal
S1J2: Tracker harness; Molex_Micro-Fit_3.0_43045-0600_2x03_P3.00mm_Horizontal
S2C1, S4C9, S6C2: 0402 100nF 50V 10% X7R; C_0402_1005Metric
S2C2: 47uF 63V - EEH-ZC1J470P; EEH_ZC1J470P
S2C4: 82uF 63V - HHXC630ARA820MJA0G; HHXC630ARA820MJA0G
S2C5, S2C6, S4C14, S4C15: 1210 10uF 50V X7R SOFT-TERM; C_1210_3225Metric
S2F1, S3F1: 0407002.WRA; Fuse_1206_3216Metric
S2Q1: SQD50P06-15L_GE3; SQD50P06-15L_GE3_tight
S2U1: LTC4412HVIS6PBF
S2Z1: PTVS33VS1UTR,115; Nexperia_CFP3_SOD-123W
S3BT1: CR123A; 1051_KEY
S3C1: 0603 2.2uF 25V 10% X7R; C_0603_1608Metric
S3U1: LM66100DCKR; SOT-363_SC-70-6
S4C7, S4C8: 1210 47uF 10V 20% X7R; C_1210_3225Metric
S4C11: 0402 560pF 50V 5% C0G/NP0; C_0402_1005Metric
S4C12: 0402 10pF 50V C0G/NP0; C_0402_1005Metric
S4C13, S5C17: 0805 4.7uF 50V 10% X7R; C_0805_2012Metric
S4L1: 2.2uH XFL4020-222MEC; IND_XFL4020-222ME
S4R14: 0402 57.6K 1%; R_0402_1005Metric
S4R18: 0402 200K 1%; R_0402_1005Metric
S4R19, S6R33: 0402 909K 1% ANTI-SULFUR AEC-Q200; R_0402_1005Metric
S4R20: 0402 130K 1%; R_0402_1005Metric
S4U5: LTC3122EMSE#PBF; MSOP-12-1EP_3x4.039mm_P0.65mm_EP1.651x2.845mm
S5Q6: 2N7002; SOT-23
S5Q7: BC856B; SOT-23
S5R21: 0402 10K 5%; R_0402_1005Metric
S5R22, S5R24, S5R25, S6R39: 0402 1M 1%; R_0402_1005Metric
S6C1: 0402 100pF 50V 5% C0G/NP0; C_0402_1005Metric
S6R32: 0603 6.8M 1%; R_0603_1608Metric
S6R38: 0402 47K 5%; R_0402_1005Metric
S6U1: TLV3012AIDBVR; SOT-23-6

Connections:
CAN_H: S1J1.3, S1J2.3
CAN_L: S1J1.6, S1J2.6
EN_BOOST: S4U5.9 (SD), S6R39.1, S6U1.1 (OUT)
GND: S1J1.1, S1J2.1, S2C1.2, S2C2.2 (-), S2C4.2 (-), S2C5.2, S2C6.2, S2U1.2 (GND), S2U1.3 (CTL), S2Z1.2 (A), S3BT1.2, S3C1.2, S3U1.2 (GND), S3U1.3 (~CE), S4C7.2, S4C8.2, S4C11.2, S4C12.2, S4C13.2, S4C14.2, S4C15.2, S4R14.2, S4R20.2, S4U5.2 (PGND), S4U5.4 (PWM/SYNC), S4U5.10 (SGND), S4U5.13 (EP), S5Q6.2 (S), S6C1.2, S6C2.2, S6R33.2, S6U1.2 (V-)
IGN: S1D1.1 (K), S1J2.5, S5R21.2
IGN_CAR: S1D1.2 (A), S1J1.5
KWIRE_K: S1J1.2, S1J2.2
unnamed: S2Q1.1 (G), S2U1.5 (GATE)
unnamed: S3BT1.1, S3F1.1
unnamed: S3C1.1, S3F1.2, S3U1.1 (VIN)
unnamed: S4C11.1, S4R18.2
unnamed: S4C9.1, S4U5.12 (CAP)
unnamed: S4R19.2, S4R20.1, S4U5.8 (FB)
unnamed: S4R14.1, S4U5.6 (RT)
unnamed: S4L1.2, S4U5.1 (SW)
unnamed: S4C12.1, S4R18.1, S4U5.7 (VC)
unnamed: S4C13.1, S4U5.5 (VCC)
unnamed: S5D3.2 (A), S5Q7.3 (C)
unnamed: S5D3.1 (K), S5R21.1
unnamed: S5Q6.3 (D), S5R24.2
unnamed: S5Q7.1 (B), S5R24.1, S5R25.2
unnamed: S5C17.1, S5Q7.2 (E), S5R22.2, S5R25.1
unnamed: S6R38.2, S6R39.2, S6U1.3 (IN+)
unnamed: S6C1.1, S6R32.2, S6R33.1, S6U1.4 (IN-)
unnamed: S6R38.1, S6U1.5 (REF)
PP12V: S1J1.4, S2F1.1
PPTRACKER: S1J2.4, S2C4.1 (+), S2C5.1, S2D2.1 (K), S2Q1.3 (S), S2U1.6 (SENSE)
VBAT: S3U1.6 (VOUT), S4C7.1, S4C8.1, S4L1.1, S4U5.3 (VIN), S5R22.1, S6C2.1, S6U1.6 (V+)
VBOOST: S2D2.2 (A), S4C9.2, S4C14.1, S4C15.1, S4R19.1, S4U5.11 (VOUT), S5C17.2, S5Q6.1 (G)
VCAR: S2C1.1, S2C2.1 (+), S2C6.1, S2F1.2, S2Q1.2 (D), S2U1.1 (VIN), S2Z1.1 (K), S6R32.1

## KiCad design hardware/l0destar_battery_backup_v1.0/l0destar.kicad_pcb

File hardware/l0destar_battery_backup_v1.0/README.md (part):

# l0destar battery backup v1.0

## Overview

**NOTE: THIS HAS NOT YET BEEN BUILT OR TESTED, USE AT YOUR OWN RISK**

- This is a prototype inline battery backup module for the l0destar vehicle
  tracker. It sits in the harness between the car and the tracker and holds
  the tracker's supply at ~9V from a single CR123A lithium primary cell when
  car power is cut
- It is designed to be hand-solderable (hot air required). Every active part
  is in a leaded package: MSOP-12, SOT-23, SC70, VSSOP-8, DPAK
- The cell is a **non-rechargeable** primary in a board-mounted holder.
  Nothing on the board charges it. See [Why a primary cell](#why-a-primary-cell)
- Pin-compatible with the v3.4 tracker's 2x3 Micro-Fit harness: J1 takes the
  car harness, J2 goes to the tracker, and the CAN/K-line and ignition pins pass
  straight through
- 4-layer 63.1 x 36.2 mm board, JLC04161H-7628 stack-up, four M2 mounting
  holes. Schematic ERC and PCB DRC are clean apart from the expected items
  listed under [Notes](#notes)

## Disclaimer

This is a prototype, not a product. Nothing here is validated or certified,
the parts lists are examples rather than a verified BOM, and every number
below is a desk calculation from datasheets rather than a bench measurement -
repeat the testing yourself rather than taking any of it on trust.

I strongly recommend not using unbranded CR123 cells or buying them from less
reputable sources.

**Before building or installing anything from this repository, read the
[full disclaimer](../../DISCLAIMER.md).**

## Test status

| Item | Test | Result | Notes |
|---------|------|--------|-------|
| Input stage | 12V car input reverse polarity | NOT TESTED | S1U1/S1Q1 ideal diode blocks; S1Z1 conducts forward into S1F1, which should clear |
| Input stage | Pass-through drop VCAR to PPTRACKER at 50 mA and 250 mA | NOT TESTED | Expected tens of mV through S1Q1 (27 mΩ), with brief body-diode drops while the LM74610 charge pump recharges |
| Input stage | ISO 7637-2 pulse 2a and 35V load dump ride-through | NOT TESTED | S1Z1 is the tracker's 33V TVS; S1C2 47 µF + S1C6 10 µF + S1C1 on VCAR |
| Switchover | Boost enables when the car rail falls below ~10.06V | NOT TESTED | S5U1 with the 6.8M/909k divider |
| Switchover | Boost disables when the car rail returns above ~11V | NOT TESTED | Depends on the cell voltage through S5R38/S5R39, see [Notes](#notes) |
| Switchover | PPTRACKER dip during handover under a forced LTE burst | NOT TESTED | Scope on J2 pin 4; S1C4 100 µF + S1C5 10 µF carry the gap |
| Boost | 9.6V output at S4C14/S4C15 | NOT TESTED | 1.202V x (1 + 909k/130k) = 9.61V; ~9V at J2 after S1D2 |
| Boost | Output current at a 2.5V cell | NOT TESTED | Burst Mode limits to ~190 mA at 2.5V in, ~300 mA at 3V in (datasheet curves) |
| Boost | Bode plot and load step | NOT TESTED | Compensation is the datasheet 2xAA to 12V example, not tuned for this operating point |
| Cell lockout | Boost held off below 2.45V, released above 2.52V | NOT TESTED | S5U4 with 1M/1M divider and 33M feedback; test on a bench supply in place of the cell |
| Cell lockout | Re-enable paced ~0.3 s | NOT TESTED | S5R41/S5C7; S5D1 makes the disable immediate |
| Cell | Reversed cell is harmless | NOT TESTED | S3U1 blocks, VBAT sits at 0V, no backup |
| Cell | No current ever flows into the cell | NOT TESTED | Ammeter in series with the cell with the car present and during handover |
| Wake pulse | IGN pulse at boost start | NOT TESTED | Expected ~12V peak, above 8V for ~0.4 s, at J2 pin 5 |
| Wake pulse | Sleeping tracker wakes and raises `backup power` | NOT TESTED | Needs firmware with `CONFIG_APP_BACKUP_SUPPLY=y` |
| Board | Idle draw from the cell, tracker asleep | NOT TESTED | Expected ~280 µA at a 2.9V cell |
| Board | Parked drain from the car with the cell fitted | NOT TESTED | Expected ~1.6 µA from the 7.7M sense divider on top of the tracker's own draw |
| Enclosure | Board and cell fit, lid clearance over the cell | NOT TESTED | 1.9 mm above the cell by the datasheet, see [enclosure/](enclosure/) |

## Features

 - Inline between the car harness and the tracker; CAN/K-line and ignition
   pass straight through
 - ~5-10uA quiescent current in pass-through operation (untested)
 - Same input protection parts as the tracker: 2A time-lag fuse, 33V TVS
   sized to ride out suppressed load dump
 - Reverse polarity protection
 - Synchronous boost (LTC3122) with true output disconnect: the backup rail
   is 0V while the car is present, so the cell is only ever loaded during a
   cut
 - Nanopower comparator switchover (2 x TLV3012, 2.8 µA each) running
   straight from the cell: takes over below ~10.06V on the car rail
 - Cell undervoltage lockout at 2.45V with a paced restart, so a tired cell
   is stopped a few percent above its rated end voltage rather than flattened
 - Ignition wake pulse: a cut wakes a sleeping tracker immediately instead of
   at its next timed wake, and the tracker reports the cut
 - Estimated runtime on a 1500 mAh CR123A: ~200 days idle, ~58 days
   reporting hourly, ~19 days reporting every 15 minutes
 - 3D-printable two-part enclosure with the cell accessible under the lid

## Why a primary cell

A non-rechargeable cell rather than a rechargeable pack, for three reasons:

- No rechargeable 18650-format cell is rated for storage in a sun-parked car.
  The binding limit is storage temperature (+45 °C at best for Li-ion and LFP;
  +20 °C beyond three months for LTO) and a parked car reaches ~70 °C cabin
  air. A CR123A is rated to +60/+70 °C
- Cycle life is not worth paying for. The backup cycles a handful of times a
  year
- A primary turns silent ageing into an event. The boost regulates its output,
  so the tracker cannot see cell voltage - a rechargeable's calendar fade would
  be invisible until a real theft tested it. The only thing that consumes a
  primary is a power cut the tracker already alerts on, so *"did it get
  used?"* is answered in the server's alert log

The cell is a consumable. A `backup power` alert that runs for a long time
means the cell needs replacing, since it does not recover. Taking the cell
out is the storage mode.

### Ignition wake pulse

A sleeping tracker has three wake sources: its timer, the accelerometer and
ignition-present. A power cut touches none of them, so on its own it would be
found at the next timed wake. The module therefore fakes ignition for a
moment when it takes over.

The tracker's wake is level-triggered and the firmware latches it, so the
pulse only has to trip the interrupt. On an ignition wake the firmware reads
the rail first: in the backup band it is the module's pulse, so the unit
reports at once with the `backup power` alert and goes back to sleep.

Limits: a second cut within the ~40 s VBOOST decay, or a cut with the key on
and the ignition wire loaded by the car, gives no pulse; both fall back to
the timed wake.

## Board configuration

### Connectors

Both connectors are the tracker's Molex Micro-Fit 3.0 2x3 (43045-0600) with
the v3.4 pinout. J1 is the car harness, J2 goes to the tracker.

| Pin | J1 (car) | J2 (tracker) | Notes |
|-----|----------|--------------|-------|
| 1 | SPARE | SPARE | Unused by v3.4, not connected on this board |
| 2 | GND | GND | |
| 3 | CAN\_H / K | CAN\_H / K | Passed straight through |
| 4 | +12V | +12V (PPTRACKER) | Car through the ideal diode, or ~9V from the boost on backup |
| 5 | IGN | IGN | Passed straight through; the wake pulse is injected here |
| 6 | CAN\_L / L | CAN\_L / L | Passed straight through |

### Firmware

The tracker needs `CONFIG_APP_BACKUP_SUPPLY=y`. With it, a supply between
`CONFIG_APP_BACKUP_MIN_MV` (8500) and `CONFIG_APP_BACKUP_MAX_MV` (9700) with
the ignition off is treated as backup power rather than a flat car battery:
timed reports keep going, the 11.8V power-off and 12.0V sleep-safety rules
are bypassed, a `backup power` alert is raised once and a `car power
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
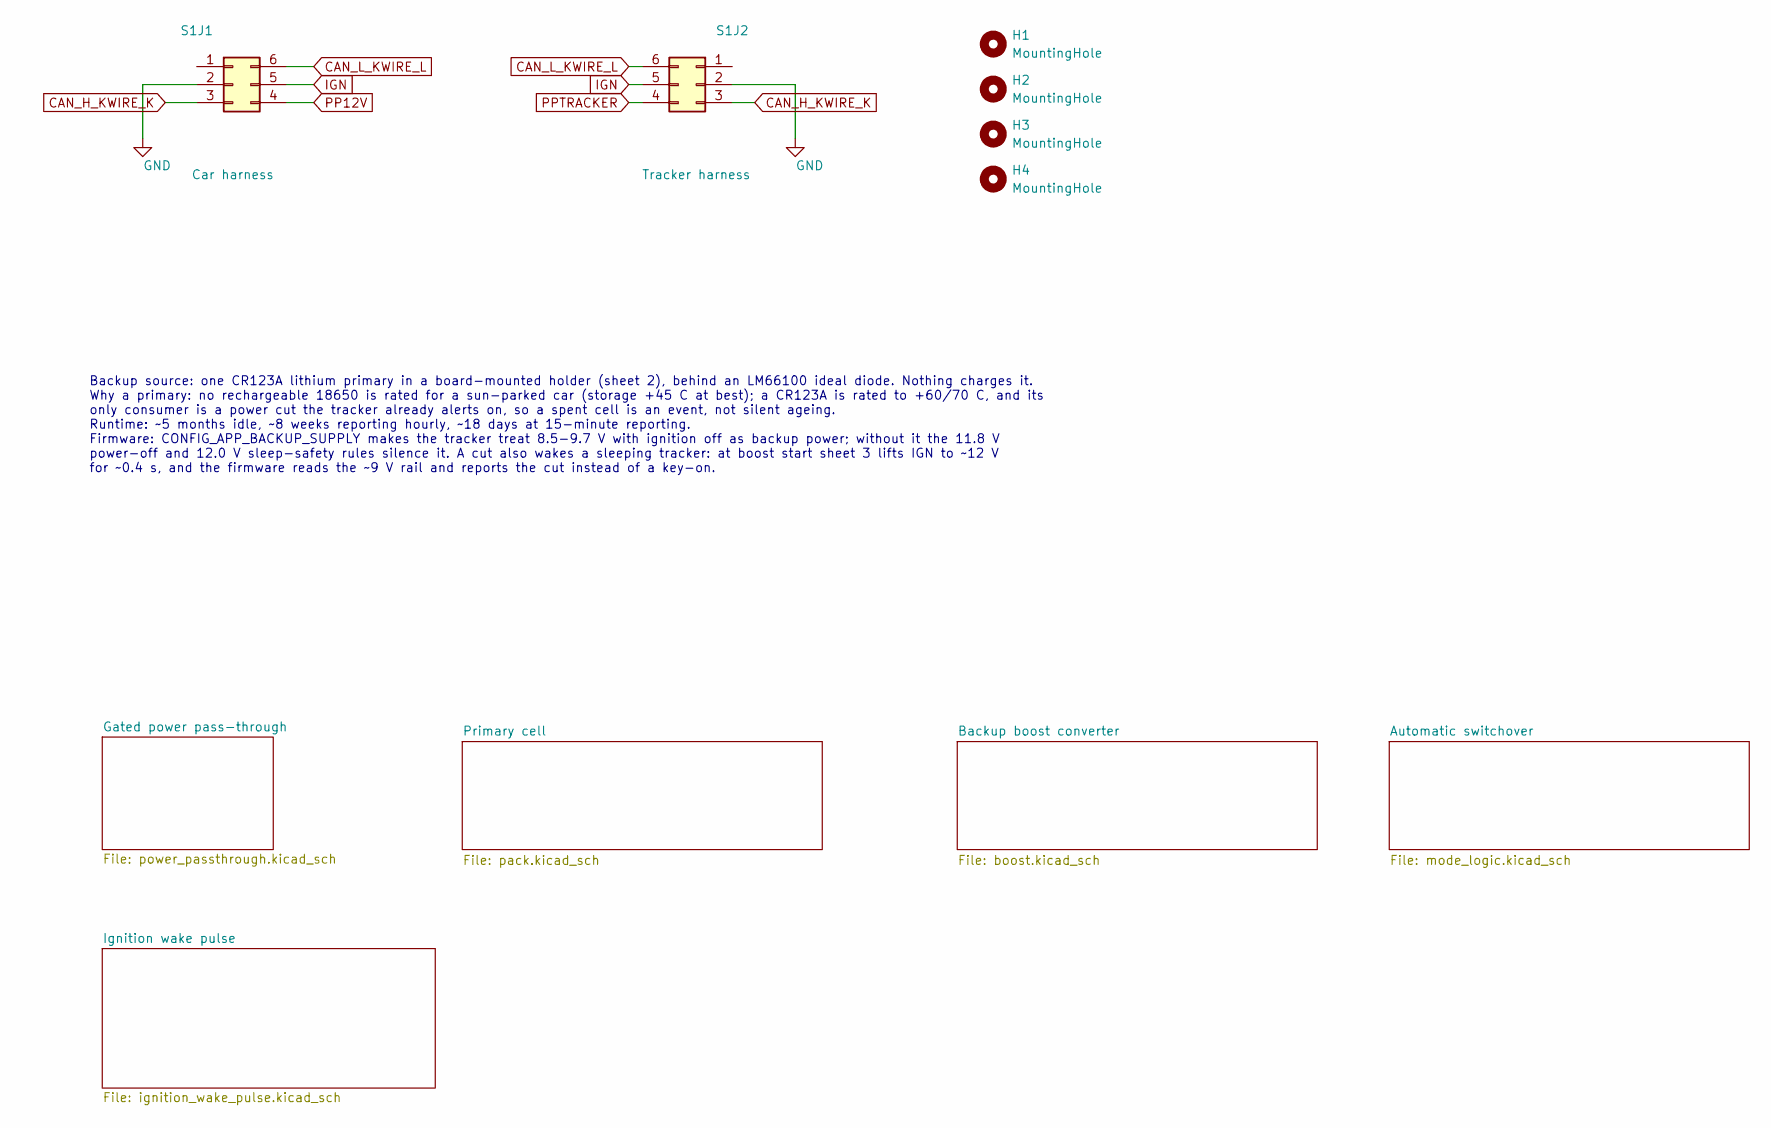
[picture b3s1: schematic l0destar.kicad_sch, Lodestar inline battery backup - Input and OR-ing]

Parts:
H1, H2, H3, H4: MountingHole; MountingHole_2.2mm_M2
S1J1: Car harness; Molex_Micro-Fit_3.0_43045-0600_2x03_P3.00mm_Horizontal
S1J2: Tracker harness; Molex_Micro-Fit_3.0_43045-0600_2x03_P3.00mm_Horizontal

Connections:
CAN_H_KWIRE_K: S1J1.3, S1J2.3
CAN_L_KWIRE_L: S1J1.6, S1J2.6
GND: S1J1.2, S1J2.2; also elsewhere on the board
IGN: S1J1.5, S1J2.5; also elsewhere on the board
PP12V: S1J1.4; also elsewhere on the board
PPTRACKER: S1J2.4; also elsewhere on the board

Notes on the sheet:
Backup source: one CR123A lithium primary in a board-mounted holder (sheet 2), behind an LM66100 ideal diode. Nothing charges it. Why a primary: no rechargeable 18650 is rated for a sun-parked car (storage +45 C at best); a CR123A is rated to +60/70 C, and its only consumer is a power cut the track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

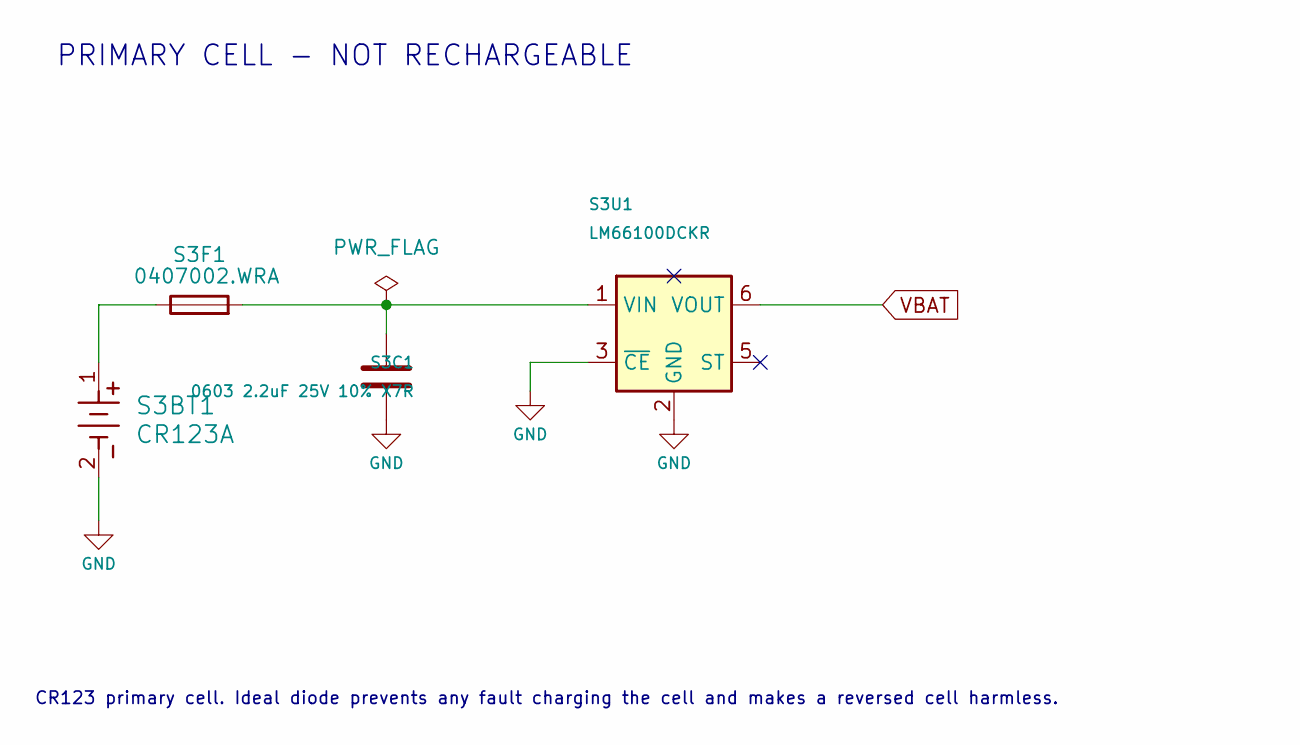
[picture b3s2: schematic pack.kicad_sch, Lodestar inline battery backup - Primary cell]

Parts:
S3BT1: CR123A; 1051_KEY; MPN 1051
S3C1: 0603 2.2uF 25V 10% X7R; C_0603_1608Metric; MPN GRM188Z71E225KE43D
S3F1: 0407002.WRA; Fuse_1206_3216Metric; MPN 0407002.WRA
S3U1: LM66100DCKR; SOT-363_SC-70-6; MPN LM66100DCKR

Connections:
GND: S3BT1.2, S3C1.2, S3U1.2 (GND), S3U1.3 (~CE); also elsewhere on the board
unnamed: S3BT1.1, S3F1.1
unnamed: S3C1.1, S3F1.2, S3U1.1 (VIN)
VBAT: S3U1.6 (VOUT); also elsewhere on the board

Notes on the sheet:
PRIMARY CELL - NOT RECHARGEABLE
CR123 primary cell. Ideal diode prevents any fault charging the cell and makes a reversed cell harmless.
